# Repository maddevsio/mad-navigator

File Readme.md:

# Mad navigator

## Description

Mad navigator is simple compass-like device shows direction to predefined geo point.
This repository contains firmware source code and schematics for device. 

## Technologies and modules

- Microcontroller [STM32F100RBT6](https://www.st.com/content/ccc/resource/technical/document/reference_manual/a2/2d/02/4b/78/57/41/a3/CD00246267.pdf/files/CD00246267.pdf/jcr:content/translations/en.CD00246267.pdf)
- LCD display [Nokia 5110](https://www.sparkfun.com/datasheets/LCD/Monochrome/Nokia5110.pdf)
- Accelerometer + gyroscope [MPU6050](https://store.invensense.com/datasheets/invensense/MPU-6050_DataSheet_V3%204.pdf)
- GPS receiver [Neo-6M](https://www.u-blox.com/sites/default/files/products/documents/NEO-6_DataSheet_%28GPS.G6-HW-09005%29.pdf)
- Magnetometer [QMC5883L](https://nettigo.pl/attachments/440)

## Prerequisites

- make
- arm-none-eabi-* (gcc, gdb, ar etc.)
- st-link utils

## Folder structure

root: Makefile, qtcreator project file (not neccessary to use it), LinkerScript

inc: All include files

src: All firmware source files

startup: Standard startup code

kicad_schema: Schematic

## How to run/debug

### RUN

Just use `make clean all program` . Make sure that your device connected via USB and you have all needed permissions.
You don't need to `make clean` every time. 

### DEBUG

1. `make clean all program`
2. run `st-util`. It will launch gdb server on localhost:4242. 
3. use arm-none-eabi-gdb

## Extended documentation

!TODO add link to medium

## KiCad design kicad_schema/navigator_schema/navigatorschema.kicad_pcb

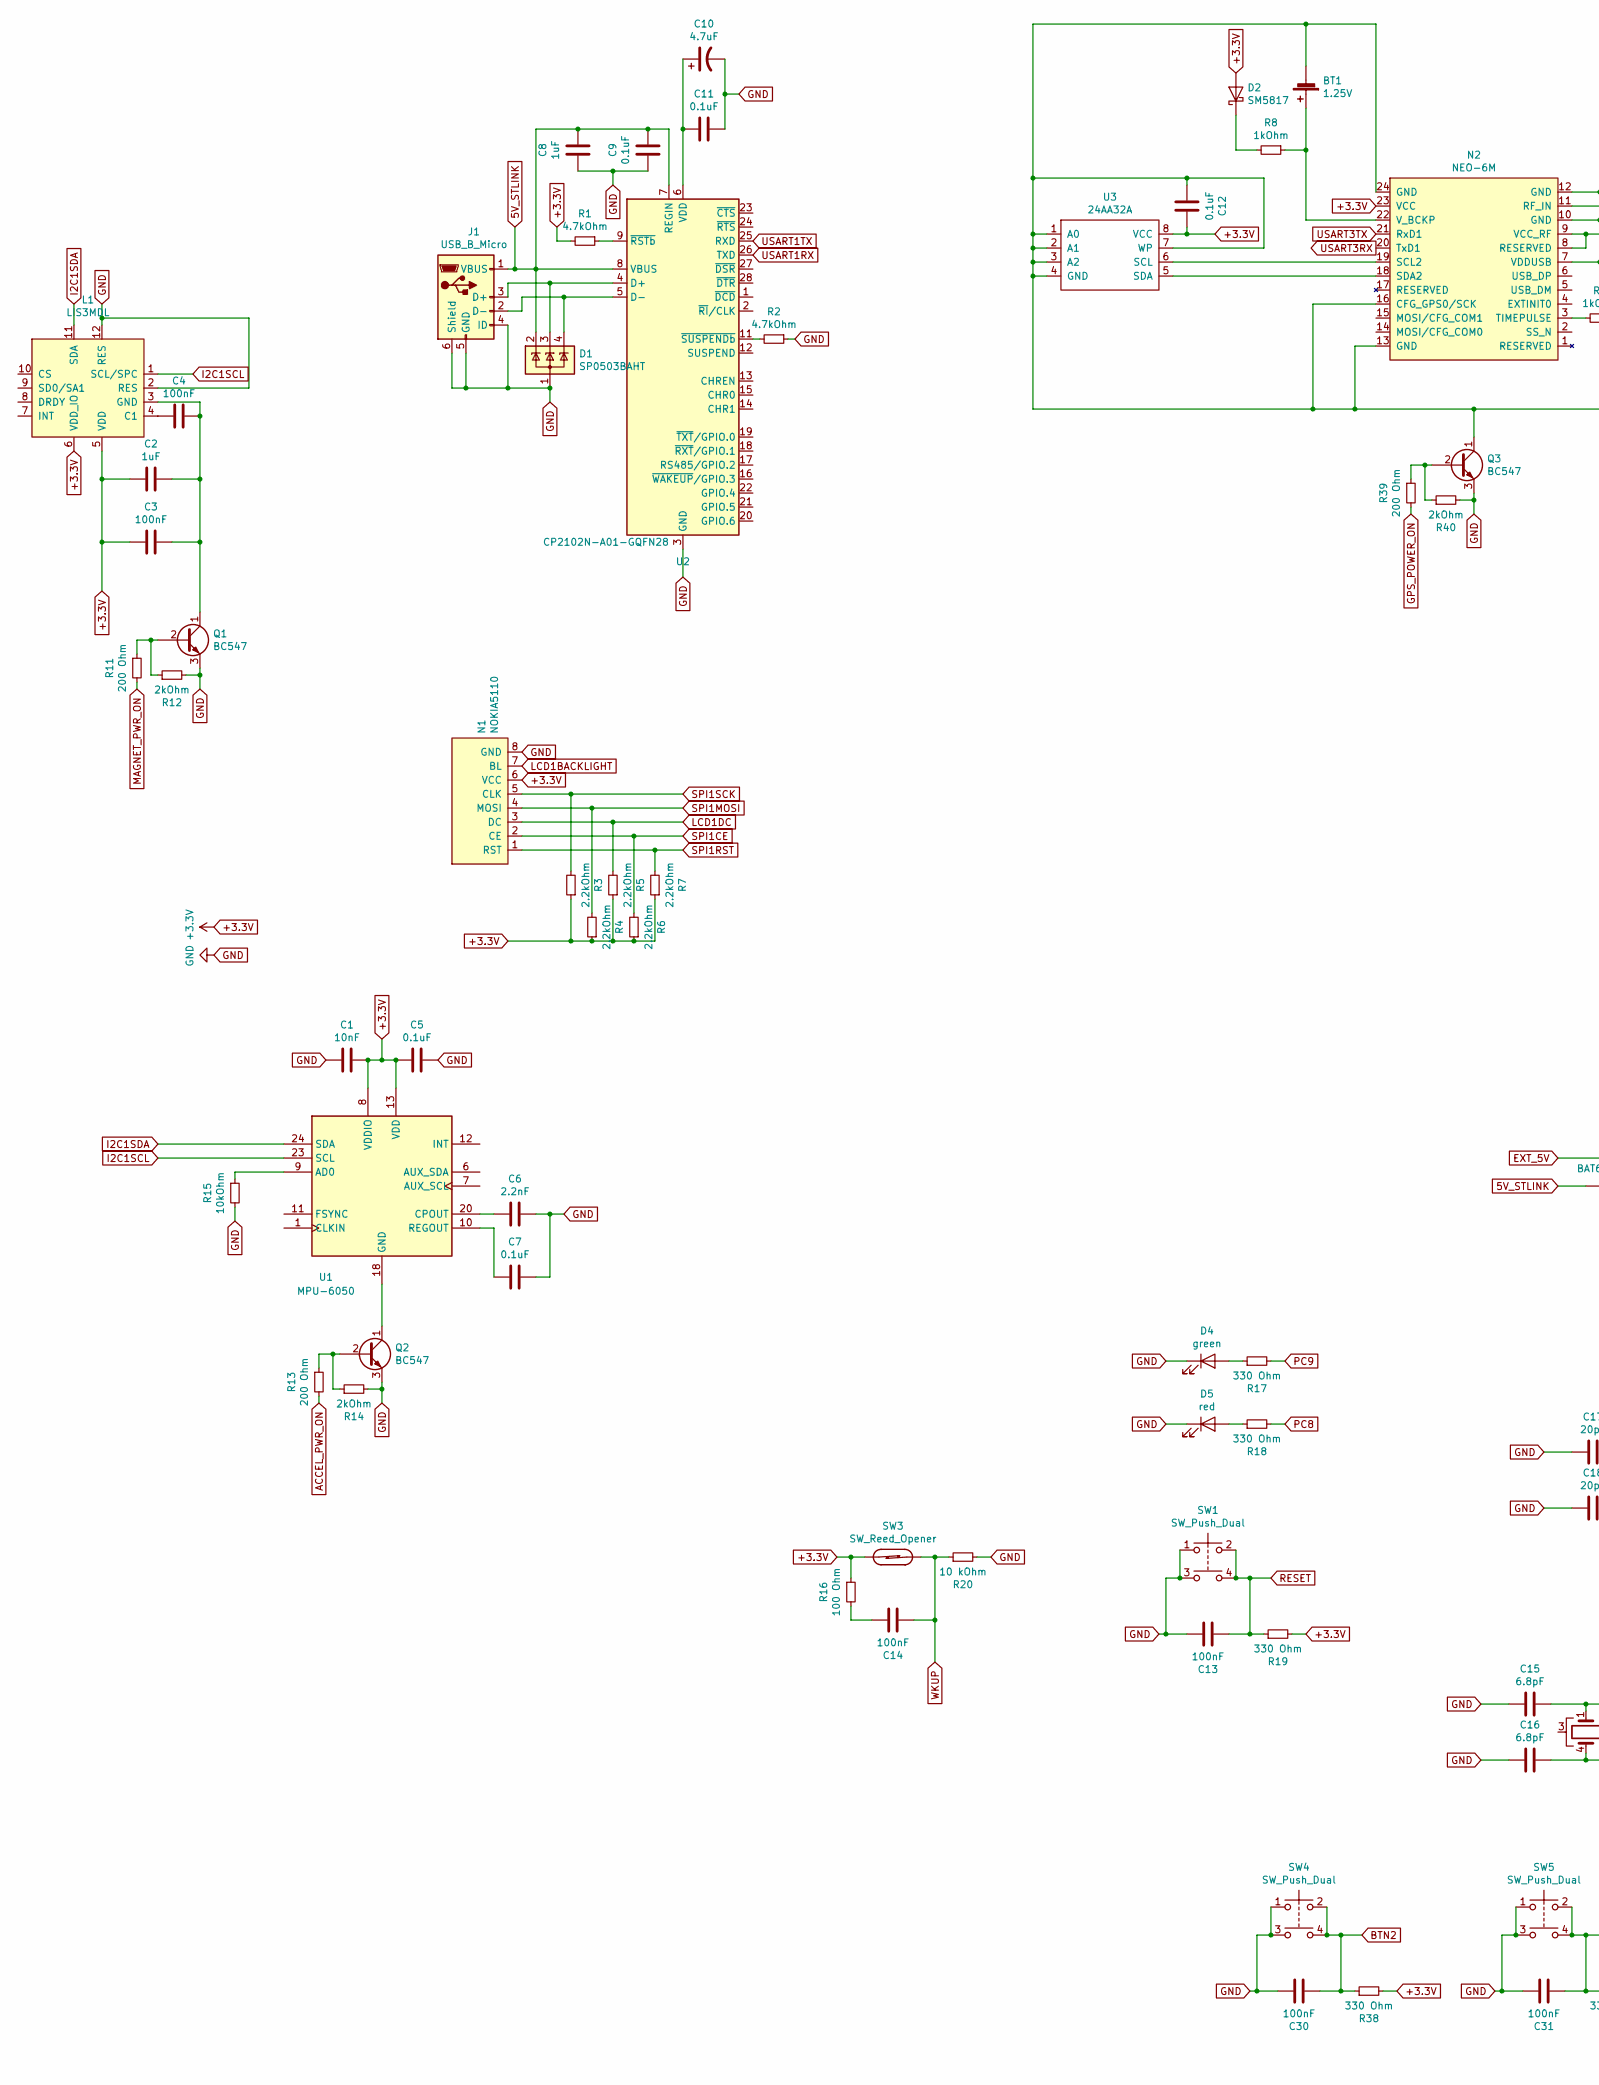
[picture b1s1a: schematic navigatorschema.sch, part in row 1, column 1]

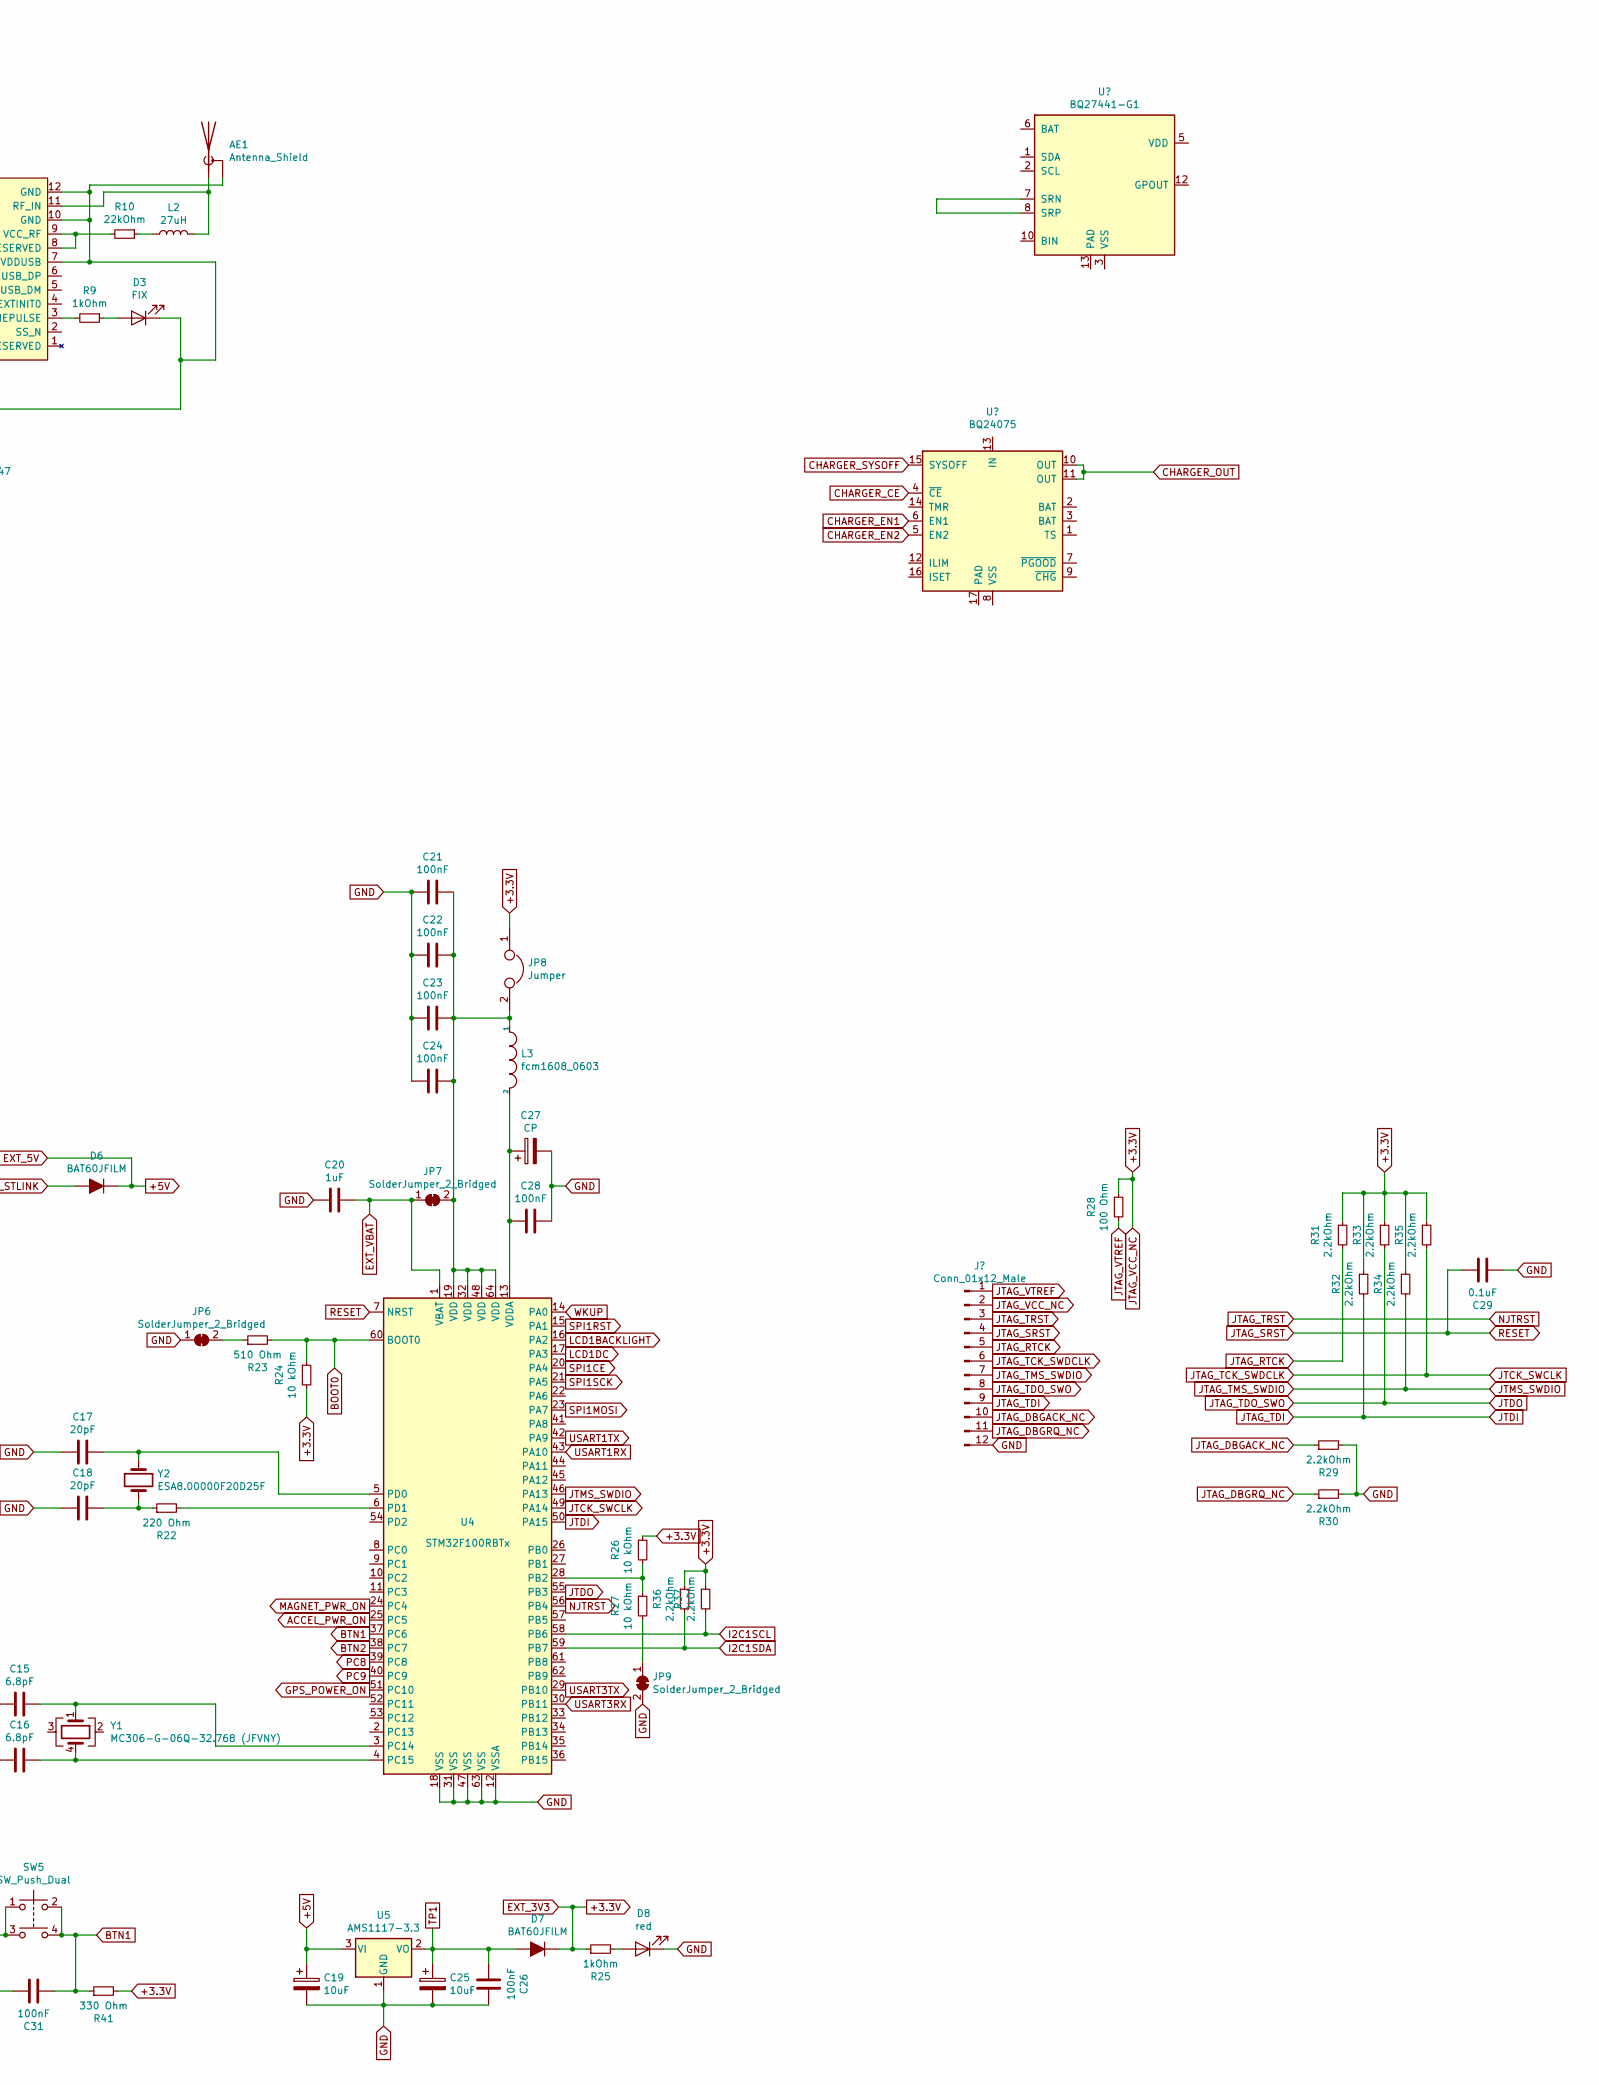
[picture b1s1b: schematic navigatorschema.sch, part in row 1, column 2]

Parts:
AE1: Antenna_Shield; U.FL_Molex_MCRF_73412-0110_Vertical
BT1: 1.25V; BatteryHolder_Seiko_MS621F
C1: 10nF; C_01005_0402Metric
C2, C8, C20: 1uF; C_01005_0402Metric
C3, C4, C13, C14, C21, C22, C23, C24, C26, C28, C30, C31: 100nF; C_01005_0402Metric
C5, C7, C9, C11, C12, C29: 0.1uF; C_01005_0402Metric
C6: 2.2nF; C_01005_0402Metric
C10: 4.7uF; C_01005_0402Metric
C15, C16: 6.8pF; C_01005_0402Metric
C17, C18: 20pF; C_01005_0402Metric
C19, C25: 10uF; C_01005_0402Metric
C27: CP; C_01005_0402Metric
D1: SP0503BAHT; SOT-143
D2: SM5817; D_MELF
D3: FIX; LED_0201_0603Metric
D4: green; LED_0201_0603Metric
D5, D8: red; LED_0201_0603Metric
D6, D7: BAT60JFILM; D_SOD-323
J1: USB_B_Micro; USB_Micro-B_Molex-105017-0001
JP6, JP7, JP9: SolderJumper_2_Bridged; SolderJumper-2_P1.3mm_Bridged2Bar_Pad1.0x1.5mm
JP8: Jumper; PinHeader_1x02_P2.54mm_Vertical
L1: LIS3MDL; LGA-12_2x2mm_P0.5mm
L2: 27uH; L_6.3x6.3_H3
L3: fcm1608_0603; L_0603_1608Metric
N1: NOKIA5110; Nokia5110_blue
N2: NEO-6M; NEO6-M
Q1, Q2, Q3: BC547; SOT-23
R1, R2: 4.7kOhm; R_0603_1608Metric
R3, R4, R5, R6, R7, R29, R30, R31, R32, R33, R34, R35, R36, R37: 2.2kOhm; R_0603_1608Metric
R8, R9, R25: 1kOhm; R_0603_1608Metric
R10: 22kOhm; R_0603_1608Metric
R11, R13, R39: 200 Ohm; R_0603_1608Metric
R12, R14, R40: 2kOhm; R_0603_1608Metric
R15: 10kOhm; R_0603_1608Metric
R16, R28: 100 Ohm; R_0603_1608Metric
R17, R18, R19, R38, R41: 330 Ohm; R_0603_1608Metric
R20, R24, R26, R27: 10 kOhm; R_0603_1608Metric
R22: 220 Ohm; R_0603_1608Metric
R23: 510 Ohm; R_0603_1608Metric
SW1, SW4, SW5: SW_Push_Dual; SW_TH_Tactile_Omron_B3F-10xx
SW3: SW_Reed_Opener; SW_SPST_REED_CT05-XXXX-G1
U1: MPU-6050; InvenSense_QFN-24_4x4mm_P0.5mm
U2: CP2102N-A01-GQFN28; QFN-28-1EP_5x5mm_P0.5mm_EP3.35x3.35mm
U3: 24AA32A; SOIC-8_3.9x4.9mm_P1.27mm
U4: STM32F100RBTx; LQFP-64_10x10mm_P0.5mm
U5: AMS1117-3.3; SOT-223-3_TabPin2
Y1: MC306-G-06Q-32.768 (JFVNY); Crystal_SMD_0603-4Pin_6.0x3.5mm
Y2: ESA8.00000F20D25F; Crystal_SMD_2012-2Pin_2.0x1.2mm

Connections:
5V_STLINK: C8.1, C9.1, D1.2 (K), D6.2 (A), J1.1 (VBUS), U2.7 (REGIN), U2.8 (VBUS)
+3.3V: C1.1, C2.1, C3.1, C5.2, C12.1, D2.2 (A), D7.1 (K), JP8.1, L1.5 (VDD), L1.6 (VDD_IO), N1.6 (VCC), N2.23 (VCC), R1.2, R3.1, R4.1, R5.1, R6.1, R7.1, R16.1, R19.2, R24.2, R25.1, R26.1, R28.1, R31.1, R32.1, R33.1, R34.1, R35.1, R36.1, R37.1, R38.2, R41.2, SW3.1, U1.8 (VDDIO), U1.13 (VDD), U3.8 (VCC); also elsewhere on the board
+5V: C19.1, D6.1 (K), U5.3 (VI)
ACCEL_PWR_ON: R13.2, U4.25 (PC5)
BOOT0: R23.2, R24.1, U4.60 (BOOT0)
BTN1: C31.2, R41.1, SW5.2, SW5.4, U4.37 (PC6)
BTN2: C30.2, R38.1, SW4.2, SW4.4, U4.38 (PC7)
EXT_VBAT: C20.1, JP7.1 (A), U4.1 (VBAT)
GND: C1.2, C5.1, C6.2, C7.2, C8.2, C9.2, C10.2, C11.1, C13.1, C15.2, C16.2, C17.2, C18.2, C19.2, C20.2, C21.2, C22.2, C23.2, C24.2, C25.2, C26.1, C27.2, C28.1, C29.2, C30.1, C31.1, D1.1 (A), D4.1 (K), D5.1 (K), D8.1 (K), J1.4 (ID), J1.5 (GND), J1.6 (Shield), JP6.1 (A), JP9.2 (B), L1.2 (RES), L1.12 (RES), N1.8 (GND), Q1.3 (E), Q2.3 (E), Q3.3 (E), R2.1, R12.2, R14.2, R15.2, R20.2, R29.2, R30.2, R40.2, SW1.1, SW1.3, SW4.1, SW4.3, SW5.1, SW5.3, U2.3 (GND), U2.29 (GND), U4.12 (VSSA), U4.18 (VSS), U4.31 (VSS), U4.47 (VSS), U4.63 (VSS), U5.1 (GND); also elsewhere on the board
GPS_POWER_ON: R39.2, U4.51 (PC10)
I2C1SCL: L1.1 (SCL/SPC), R37.2, U1.23 (SCL), U4.58 (PB6)
I2C1SDA: L1.11 (SDA), R36.2, U1.24 (SDA), U4.59 (PB7)
JTCK_SWCLK: R35.2, U4.49 (PA14); also elsewhere on the board
JTDI: R32.2, U4.50 (PA15); also elsewhere on the board
JTDO: R33.2, U4.55 (PB3); also elsewhere on the board
JTMS_SWDIO: R34.2, U4.46 (PA13); also elsewhere on the board
LCD1BACKLIGHT: N1.7 (BL), U4.16 (PA2)
LCD1DC: N1.3 (DC), R5.2, U4.17 (PA3)
MAGNET_PWR_ON: R11.2, U4.24 (PC4)
NJTRST: U4.56 (PB4); also elsewhere on the board
unnamed: AE1.1 (A), L2.2, N2.11 (RF_IN)
unnamed: BT1.1 (+), N2.22 (V_BCKP), R8.1
unnamed: C2.2, C3.2, C4.2, L1.3 (GND), Q1.1 (C)
unnamed: C4.1, L1.4 (C1)
unnamed: C6.1, U1.20 (CPOUT)
unnamed: C7.1, U1.10 (REGOUT)
unnamed: C10.1, C11.2, U2.6 (VDD)
unnamed: C14.1, R16.2
unnamed: C15.1, U4.3 (PC14), Y1.1
unnamed: C16.1, U4.4 (PC15), Y1.4
unnamed: C17.1, U4.5 (PD0), Y2.1
unnamed: C18.1, R22.1, Y2.2
unnamed: C21.1, C22.1, C23.1, C24.1, JP7.2 (B), JP8.2, L3.1, U4.19 (VDD), U4.32 (VDD), U4.48 (VDD), U4.64 (VDD)
unnamed: C27.1, C28.2, L3.2, U4.13 (VDDA)
unnamed: D1.3 (K), J1.3 (D+), U2.4 (D+)
unnamed: D1.4 (K), J1.2 (D-), U2.5 (D-)
unnamed: D2.1 (K), R8.2
unnamed: D3.2 (A), R9.1
unnamed: D4.2 (A), R17.1
unnamed: D5.2 (A), R18.1
unnamed: D8.2 (A), R25.2
unnamed 41: R28.2; also elsewhere on the board
unnamed 42: R31.2; also elsewhere on the board
unnamed 43: R30.1; also elsewhere on the board
unnamed 44: R29.1; also elsewhere on the board
unnamed: JP6.2 (B), R23.1
unnamed: JP9.1 (A), R27.2
unnamed: L2.1, R10.1
unnamed: N2.3 (TIMEPULSE), R9.2
unnamed: N2.8 (RESERVED), N2.9 (VCC_RF), R10.2
unnamed: N2.18 (SDA2), U3.5 (SDA)
unnamed: N2.19 (SCL2), U3.6 (SCL)
unnamed: Q1.2 (B), R11.1, R12.1
unnamed: Q2.1 (C), U1.18 (GND)
unnamed: Q2.2 (B), R13.1, R14.1
unnamed: Q3.2 (B), R39.1, R40.1
unnamed: R1.1, U2.9 (~RSTb)
unnamed: R2.2, U2.11 (~SUSPENDb)
unnamed: R15.1, U1.9 (AD0)
unnamed: R22.2, U4.6 (PD1)
unnamed: R26.2, R27.1, U4.28 (PB2)
PC8: R18.2, U4.39 (PC8)
PC9: R17.2, U4.40 (PC9)
RESET: C13.2, C29.1, R19.1, SW1.2, SW1.4, U4.7 (NRST); also elsewhere on the board
SPI1CE: N1.2 (CE), R6.2, U4.20 (PA4)
SPI1MOSI: N1.4 (MOSI), R4.2, U4.23 (PA7)
SPI1RST: N1.1 (RST), R7.2, U4.15 (PA1)
SPI1SCK: N1.5 (CLK), R3.2, U4.21 (PA5)
TP1: C25.1, C26.2, D7.2 (A), U5.2 (VO)
USART1RX: U2.26 (TXD), U4.43 (PA10)
USART1TX: U2.25 (RXD), U4.42 (PA9)
USART3RX: N2.20 (TxD1), U4.30 (PB11)
USART3TX: N2.21 (RxD1), U4.29 (PB10)
WKUP: C14.2, R20.1, SW3.2, U4.14 (PA0); also elsewhere on the board

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
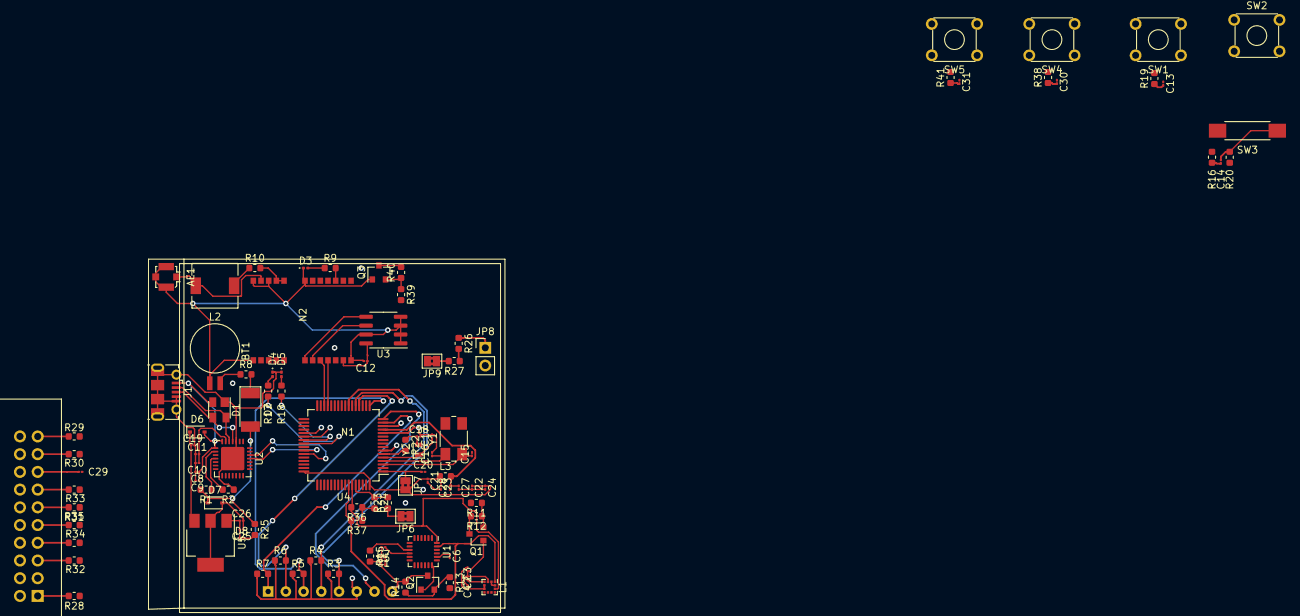
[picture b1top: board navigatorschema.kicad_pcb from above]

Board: 2 copper layers, 107 parts (0 on the bottom side), 75 nets.

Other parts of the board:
J4: Conn_ARM_JTAG_SWD_20; IDC-Header_2x10_P2.54mm_Vertical
SW2: SW_Push_Dual; SW_TH_Tactile_Omron_B3F-10xx

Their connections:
+3.3V: J4.2, SW2.1, SW2.3; also elsewhere on the board
GND: J4.4, J4.6, J4.8, J4.10, J4.12, J4.14, J4.16, J4.18, J4.20; also elsewhere on the board
JTCK_SWCLK: J4.9; also elsewhere on the board
JTDI: J4.5; also elsewhere on the board
JTDO: J4.13; also elsewhere on the board
JTMS_SWDIO: J4.7; also elsewhere on the board
NJTRST: J4.3; also elsewhere on the board
unnamed 41: J4.1; also elsewhere on the board
unnamed 42: J4.11; also elsewhere on the board
unnamed 43: J4.17; also elsewhere on the board
unnamed 44: J4.19; also elsewhere on the board
RESET: J4.15; also elsewhere on the board
WKUP: SW2.2, SW2.4; also elsewhere on the board
